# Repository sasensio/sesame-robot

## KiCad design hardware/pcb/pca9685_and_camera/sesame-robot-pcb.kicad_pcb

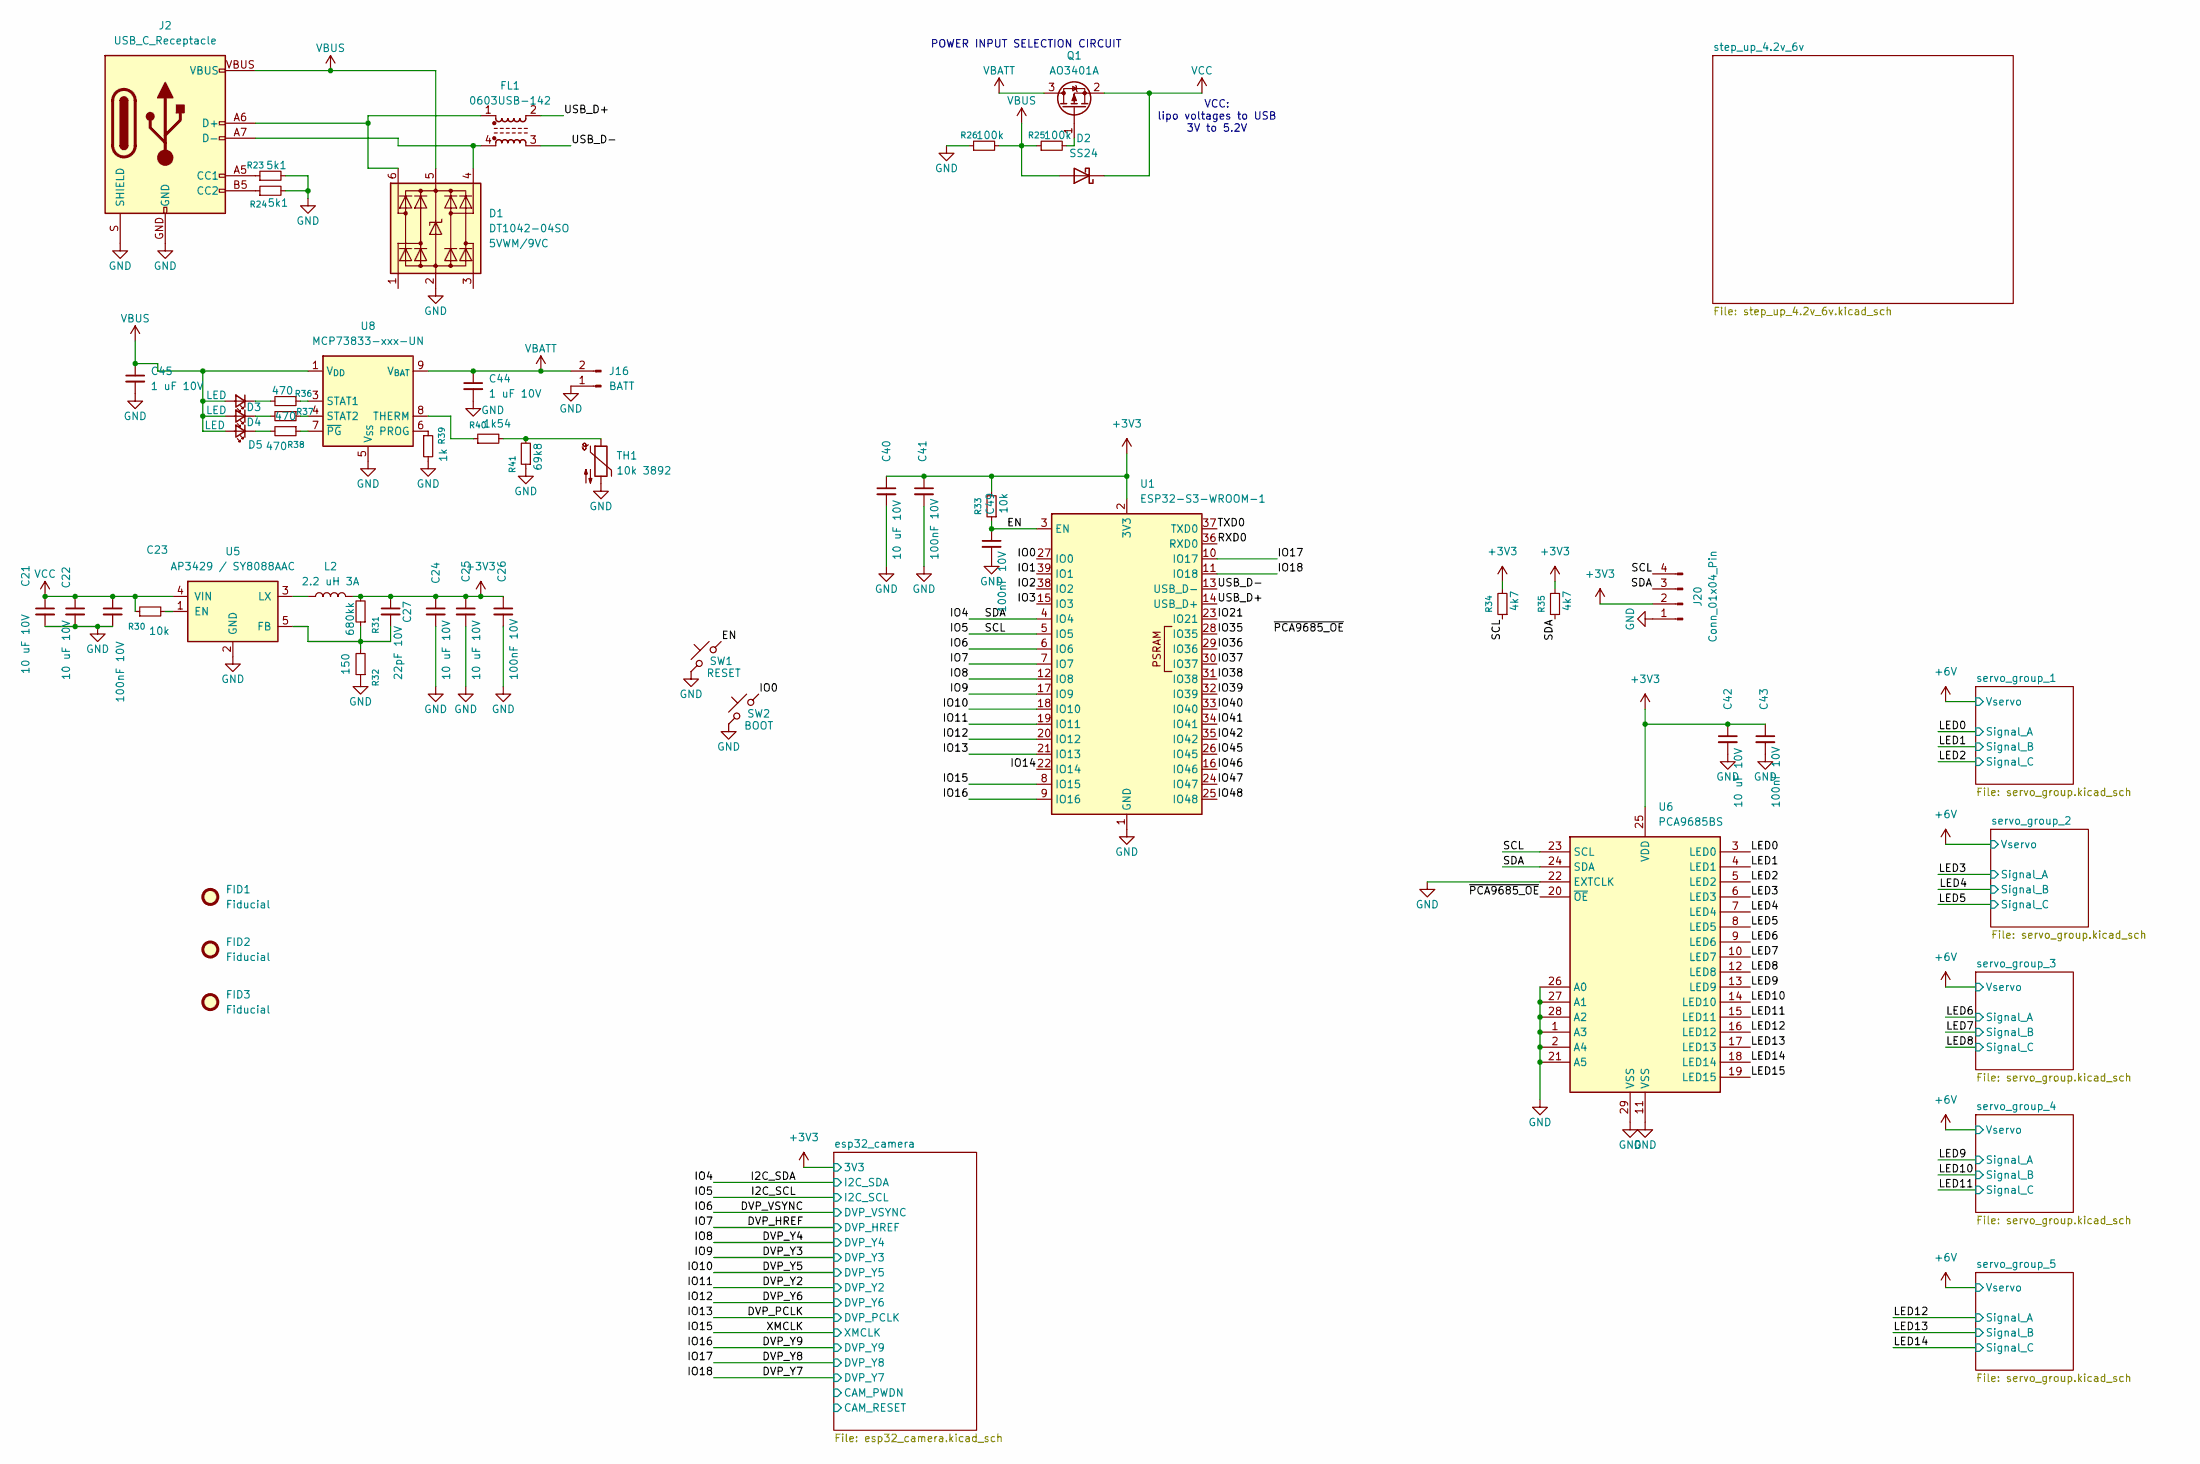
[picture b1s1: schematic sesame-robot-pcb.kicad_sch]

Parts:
C21, C22, C24, C25, C40, C42: 10 uF 10V; C_0603_1608Metric
C23, C26, C41, C43, C49: 100nF 10V; C_0402_1005Metric
C27: 22pF 10V; C_0402_1005Metric
C44, C45: 1 uF 10V; C_0603_1608Metric
D1: DT1042-04SO; SOT23-6; Rating 5VWM/9VC
D2: SS24; D_SMA
D3, D4, D5: LED; LED_0603_1608Metric
FID1, FID2, FID3: Fiducial; Fiducial_0.5mm_Mask1.5mm
FL1: 0603USB-142; L_CommonModeChoke_Coilcraft_0603USB
J2: USB_C_Receptacle; USB-C_16
J16: BATT; JST_PH_B2B-PH-K_1x02_P2.00mm_Vertical
J20: Conn_01x04_Pin; PinHeader_1x04_P2.54mm_Vertical
L2: 2.2 uH 3A; L_1206_3216Metric
Q1: AO3401A; SOT-23
R23, R24: 5k1; R_0402_1005Metric
R25, R26: 100k; R_0603_1608Metric
R30, R33: 10k; R_0603_1608Metric
R31: 680kk; R_0603_1608Metric
R32: 150; R_0603_1608Metric
R34, R35: 4k7; R_0603_1608Metric
R36, R37, R38: 470; R_0402_1005Metric
R39: 1k; R_0603_1608Metric
R40: 1k54; R_0402_1005Metric
R41: 69k8; R_0402_1005Metric
SW1: RESET; SW_SPST_EVQP2_MiddlePushTravel_H2.5mm
SW2: BOOT; SW_SPST_EVQP2_MiddlePushTravel_H2.5mm
TH1: 10k 3892; R_Axial_DIN0204_L3.6mm_D1.6mm_P2.54mm_Vertical
U1: ESP32-S3-WROOM-1; ESP32-S3-WROOM-1U
U5: AP3429 / SY8088AAC; SOT23-5
U6: PCA9685BS; QFN-28-1EP_6x6mm_P0.65mm_EP4.25x4.25mm
U8: MCP73833-xxx-UN; MSOP-10_3x3mm_P0.5mm

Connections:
+3V3: C24.1, C25.1, C26.1, C27.1, C40.1, C41.1, C42.1, C43.1, J20.2, L2.2, R31.2, R33.2, R34.2, R35.2, U1.2 (3V3), U6.25 (VDD); also elsewhere on the board
/DVP_HREF: U1.7 (IO7); also elsewhere on the board
/DVP_PCLK: U1.21 (IO13); also elsewhere on the board
/DVP_VSYNC: U1.6 (IO6); also elsewhere on the board
/DVP_Y2: U1.19 (IO11); also elsewhere on the board
/DVP_Y3: U1.17 (IO9); also elsewhere on the board
/DVP_Y4: U1.12 (IO8); also elsewhere on the board
/DVP_Y5: U1.18 (IO10); also elsewhere on the board
/DVP_Y6: U1.20 (IO12); also elsewhere on the board
/DVP_Y7: U1.11 (IO18); also elsewhere on the board
/DVP_Y8: U1.10 (IO17); also elsewhere on the board
/DVP_Y9: U1.9 (IO16); also elsewhere on the board
/EN: C49.1, R33.1, SW1.2, U1.3 (EN)
/I2C_SCL: J20.4, R34.1, U1.5 (IO5), U6.23 (SCL); also elsewhere on the board
/I2C_SDA: J20.3, R35.1, U1.4 (IO4), U6.24 (SDA); also elsewhere on the board
/IO0: SW2.2, U1.27 (IO0)
/IO1: U1.39 (IO1)
/IO2: U1.38 (IO2)
/IO3: U1.15 (IO3)
/IO14: U1.22 (IO14)
/IO15: U1.8 (IO15); also elsewhere on the board
/IO21: U1.23 (IO21)
/IO35: U1.28 (IO35)
/IO36: U1.29 (IO36)
/IO37: U1.30 (IO37)
/IO38: U1.31 (IO38)
/IO39: U1.32 (IO39)
/IO40: U1.33 (IO40)
/IO41: U1.34 (IO41)
/IO42: U1.35 (IO42)
/IO45: U1.26 (IO45)
/IO46: U1.16 (IO46)
/IO47: U1.24 (IO47)
/IO48: U1.25 (IO48)
/LED0: U6.3 (LED0); also elsewhere on the board
/LED1: U6.4 (LED1); also elsewhere on the board
/LED2: U6.5 (LED2); also elsewhere on the board
/LED3: U6.6 (LED3); also elsewhere on the board
/LED4: U6.7 (LED4); also elsewhere on the board
/LED5: U6.8 (LED5); also elsewhere on the board
/LED6: U6.9 (LED6); also elsewhere on the board
/LED7: U6.10 (LED7); also elsewhere on the board
/LED8: U6.12 (LED8); also elsewhere on the board
/LED9: U6.13 (LED9); also elsewhere on the board
/LED10: U6.14 (LED10); also elsewhere on the board
/LED11: U6.15 (LED11); also elsewhere on the board
/LED12: U6.16 (LED12); also elsewhere on the board
/LED13: U6.17 (LED13); also elsewhere on the board
/LED14: U6.18 (LED14); also elsewhere on the board
/LED15: U6.19 (LED15)
/RXD0: U1.36 (RXD0)
/TXD0: U1.37 (TXD0)
/USB_D+: FL1.2, U1.14 (USB_D+)
/USB_D-: FL1.3, U1.13 (USB_D-)
/~PCA9685_OE: U6.20 (~OE)
GND: C21.2, C22.2, C23.2, C24.2, C25.2, C26.2, C40.2, C41.2, C42.2, C43.2, C44.2, C45.2, C49.2, D1.2 (GND), J2.GND, J2.S (SHIELD), J16.1, J20.1, R23.2, R24.2, R26.1, R32.1, R39.2, R41.1, SW1.1, SW2.1, TH1.2, U1.1 (GND), U1.40 (GND), U1.41 (GND), U5.2 (GND), U6.1 (A3), U6.2 (A4), U6.11 (VSS), U6.21 (A5), U6.22 (EXTCLK), U6.26 (A0), U6.27 (A1), U6.28 (A2), U6.29 (VSS), U8.5 (V_{SS}); also elsewhere on the board
unnamed: D1.4 (I/O3), FL1.4, J2.A7 (D-), J2.B7 (D-)
unnamed: D1.6 (I/O4), FL1.1, J2.A6 (D+), J2.B6 (D+)
unnamed: D3.1 (K), R36.2
unnamed: D4.1 (K), R37.2
unnamed: D5.1 (K), R38.2
unnamed: J2.A5 (CC1), R23.1
unnamed: J2.B5 (CC2), R24.1
unnamed: Q1.1 (G), R25.2
unnamed: R40.2, R41.2, TH1.1
unnamed: R30.2, U5.1 (EN)
unnamed: C27.2, R31.1, R32.2, U5.5 (FB)
unnamed: L2.1, U5.3 (LX)
unnamed: R39.1, U8.6 (PROG)
unnamed: R36.1, U8.3 (STAT1)
unnamed: R37.1, U8.4 (STAT2)
unnamed: R40.1, U8.8 (THERM)
unnamed: R38.1, U8.7 (~PG)
VBATT: C44.1, J16.2, Q1.3 (D), U8.9 (V_{BAT}), U8.10 (V_{BAT})
VBUS: C45.1, D1.5 (VCC), D2.2 (A), D3.2 (A), D4.2 (A), D5.2 (A), J2.VBUS, R25.1, R26.2, U8.1 (V_{DD}), U8.2 (V_{DD})
VCC: C21.1, C22.1, C23.1, D2.1 (K), Q1.2 (S), R30.1, U5.4 (VIN); also elsewhere on the board

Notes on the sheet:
VCC: lipo voltages to USB 3V to 5.2V
POWER INPUT SELECTION CIRCUIT

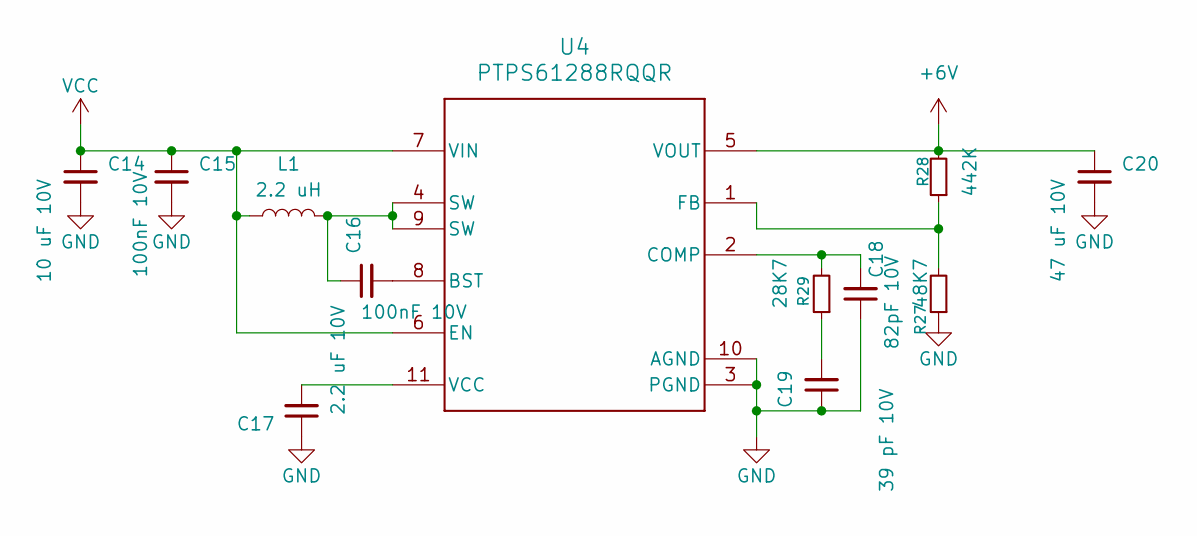
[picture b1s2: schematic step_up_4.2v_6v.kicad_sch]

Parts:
C14: 10 uF 10V; C_0603_1608Metric
C15, C16: 100nF 10V; C_0402_1005Metric
C17: 2.2 uF 10V; C_0603_1608Metric
C18: 82pF 10V; C_0402_1005Metric
C19: 39 pF 10V; C_0402_1005Metric
C20: 47 uF 10V; C_1206_3216Metric
L1: 2.2 uH; L_TDK_VLS6045EX_VLS6045AF; mpn# SRP5030HMT-1R0M
R27: 48K7; R_0603_1608Metric
R28: 442K; R_0603_1608Metric
R29: 28K7; R_0603_1608Metric
U4: PTPS61288RQQR; RQQ0011A-MFG

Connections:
+6V: C20.1, R28.2, U4.5 (VOUT); also elsewhere on the board
GND: C14.2, C15.2, C17.1, C18.1, C19.1, C20.2, R27.1, U4.3 (PGND), U4.10 (AGND); also elsewhere on the board
unnamed: C16.1, L1.2, U4.4 (SW), U4.9 (SW)
unnamed: C19.2, R29.1
unnamed: C16.2, U4.8 (BST)
unnamed: C18.2, R29.2, U4.2 (COMP)
unnamed: R27.2, R28.1, U4.1 (FB)
unnamed: C17.2, U4.11 (VCC)
VCC: C14.1, C15.1, L1.1, U4.6 (EN), U4.7 (VIN); also elsewhere on the board

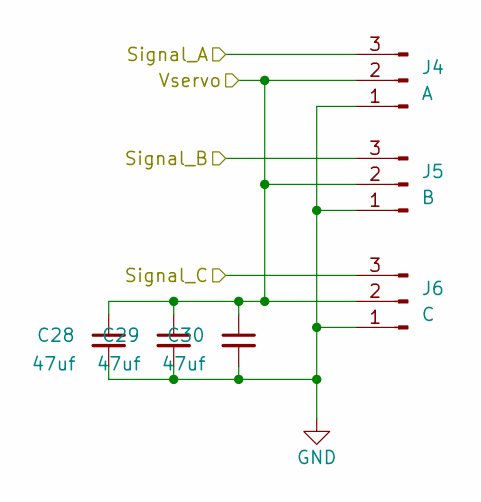
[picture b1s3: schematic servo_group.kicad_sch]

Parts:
C28, C29, C30: 47uf; C_1206_3216Metric
J4: A; PinHeader_1x03_P2.54mm_Vertical
J5: B; PinHeader_1x03_P2.54mm_Vertical
J6: C; PinHeader_1x03_P2.54mm_Vertical

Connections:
+6V: C28.1, C29.1, C30.1, J4.2, J5.2, J6.2; also elsewhere on the board
/LED0: J4.3; also elsewhere on the board
/LED1: J5.3; also elsewhere on the board
/LED2: J6.3; also elsewhere on the board
GND: C28.2, C29.2, C30.2, J4.1, J5.1, J6.1; also elsewhere on the board

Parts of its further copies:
C31, C32, C33, C34, C35, C36, C37, C38, C39, C46, C47, C48: 47uf; C_1206_3216Metric
J7, J10, J13, J17: A; PinHeader_1x03_P2.54mm_Vertical
J8, J11, J14, J18: B; PinHeader_1x03_P2.54mm_Vertical
J9, J12, J15, J19: C; PinHeader_1x03_P2.54mm_Vertical

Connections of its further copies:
+6V: C31.1, C32.1, C33.1, C34.1, C35.1, C36.1, C37.1, C38.1, C39.1, C46.1, C47.1, C48.1, J7.2, J8.2, J9.2, J10.2, J11.2, J12.2, J13.2, J14.2, J15.2, J17.2, J18.2, J19.2; also elsewhere on the board
/LED3: J7.3; also elsewhere on the board
/LED4: J8.3; also elsewhere on the board
/LED5: J9.3; also elsewhere on the board
/LED6: J10.3; also elsewhere on the board
/LED7: J11.3; also elsewhere on the board
/LED8: J12.3; also elsewhere on the board
/LED9: J13.3; also elsewhere on the board
/LED10: J14.3; also elsewhere on the board
/LED11: J15.3; also elsewhere on the board
/LED12: J17.3; also elsewhere on the board
/LED13: J18.3; also elsewhere on the board
/LED14: J19.3; also elsewhere on the board
GND: C31.2, C32.2, C33.2, C34.2, C35.2, C36.2, C37.2, C38.2, C39.2, C46.2, C47.2, C48.2, J7.1, J8.1, J9.1, J10.1, J11.1, J12.1, J13.1, J14.1, J15.1, J17.1, J18.1, J19.1; also elsewhere on the board

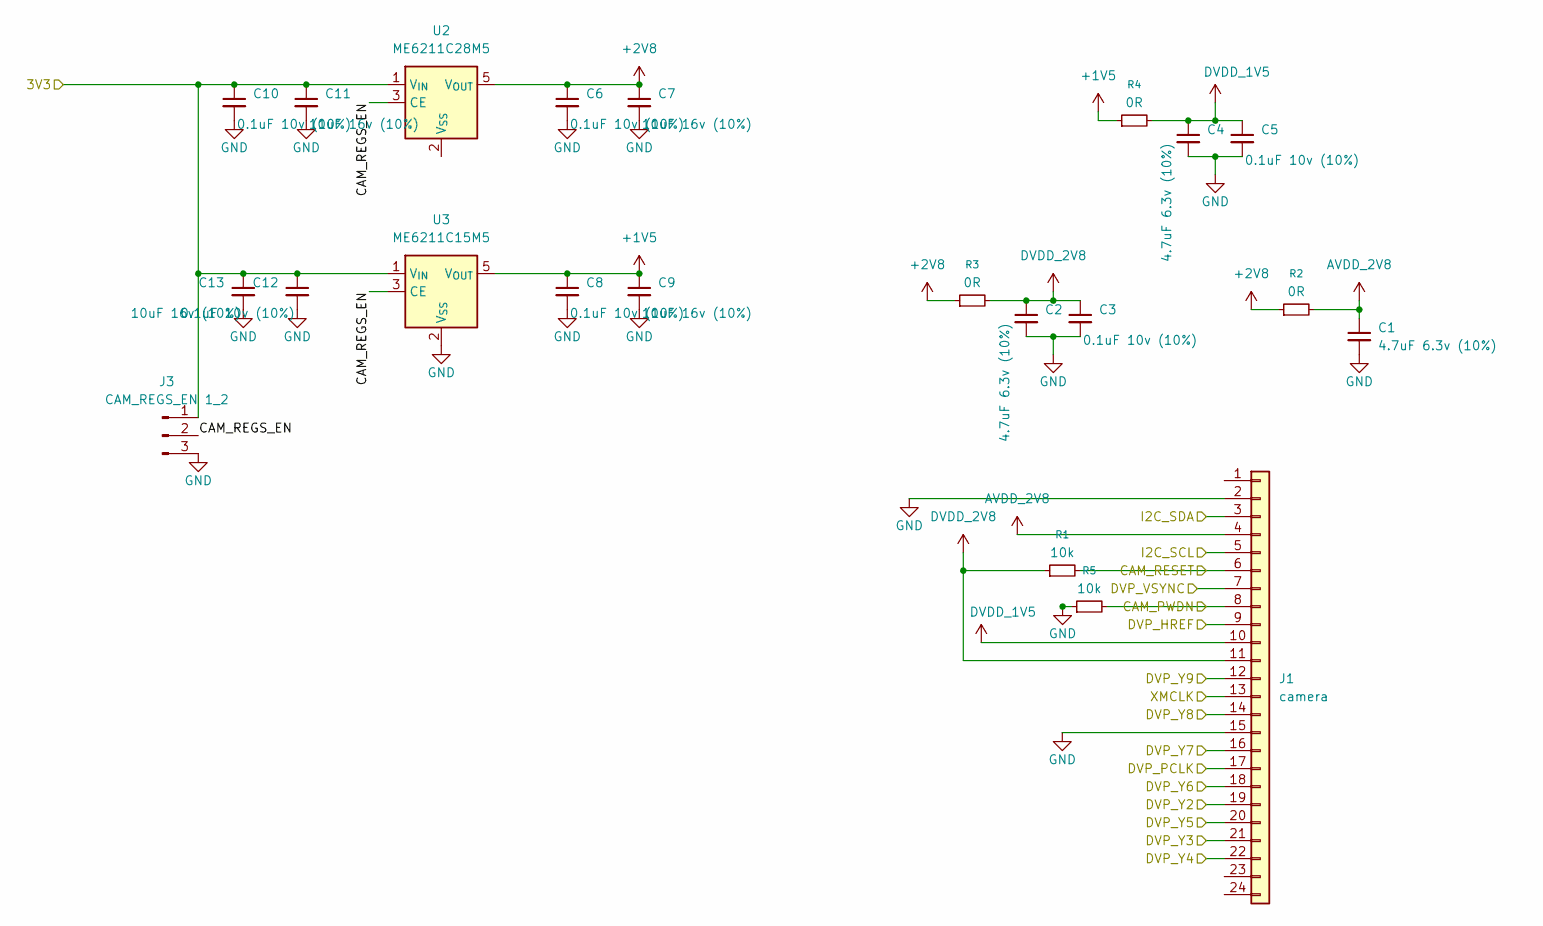
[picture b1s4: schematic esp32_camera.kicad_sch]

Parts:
C1, C2, C4: 4.7uF 6.3v (10%); C_0402_1005Metric
C3, C5, C6, C8, C10, C12: 0.1uF 10v (10%); C_0402_1005Metric
C7, C9, C11, C13: 10uF 16v (10%); C_0603_1608Metric
J1: camera; FPC_1x24_P0.5mm_Horizontal_DualContact
J3: CAM_REGS_EN 1_2; PinHeader_1x03_P2.00mm_Vertical
R1, R5: 10k; R_0603_1608Metric
R2, R3, R4: 0R; R_0402_1005Metric
U2: ME6211C28M5; SOT-23-5
U3: ME6211C15M5; SOT-23-5

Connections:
+1V5: C8.1, C9.1, R4.1, U3.5 (V_{OUT})
+2V8: C6.1, C7.1, R2.1, R3.1, U2.5 (V_{OUT})
+3V3: C10.1, C11.1, C12.1, C13.1, J3.1, U2.1 (V_{IN}), U3.1 (V_{IN}); also elsewhere on the board
/DVP_HREF: J1.9; also elsewhere on the board
/DVP_PCLK: J1.17; also elsewhere on the board
/DVP_VSYNC: J1.7; also elsewhere on the board
/DVP_Y2: J1.19; also elsewhere on the board
/DVP_Y3: J1.21; also elsewhere on the board
/DVP_Y4: J1.22; also elsewhere on the board
/DVP_Y5: J1.20; also elsewhere on the board
/DVP_Y6: J1.18; also elsewhere on the board
/DVP_Y7: J1.16; also elsewhere on the board
/DVP_Y8: J1.14; also elsewhere on the board
/DVP_Y9: J1.12; also elsewhere on the board
/I2C_SCL: J1.5; also elsewhere on the board
/I2C_SDA: J1.3; also elsewhere on the board
/IO15: J1.13; also elsewhere on the board
/esp32_camera/CAM_PWDN: J1.8, R5.2
/esp32_camera/CAM_REGS_EN: J3.2, U2.3 (CE), U3.3 (CE)
/esp32_camera/CAM_RESET: J1.6, R1.2
AVDD_2V8: C1.1, J1.4, R2.2
DVDD_1V5: C4.1, C5.1, J1.10, R4.2
DVDD_2V8: C2.1, C3.1, J1.11, R1.1, R3.2
GND: C1.2, C2.2, C3.2, C4.2, C5.2, C6.2, C7.2, C8.2, C9.2, C10.2, C11.2, C12.2, C13.2, J1.2, J1.15, J3.3, R5.1, U3.2 (V_{SS}); also elsewhere on the board

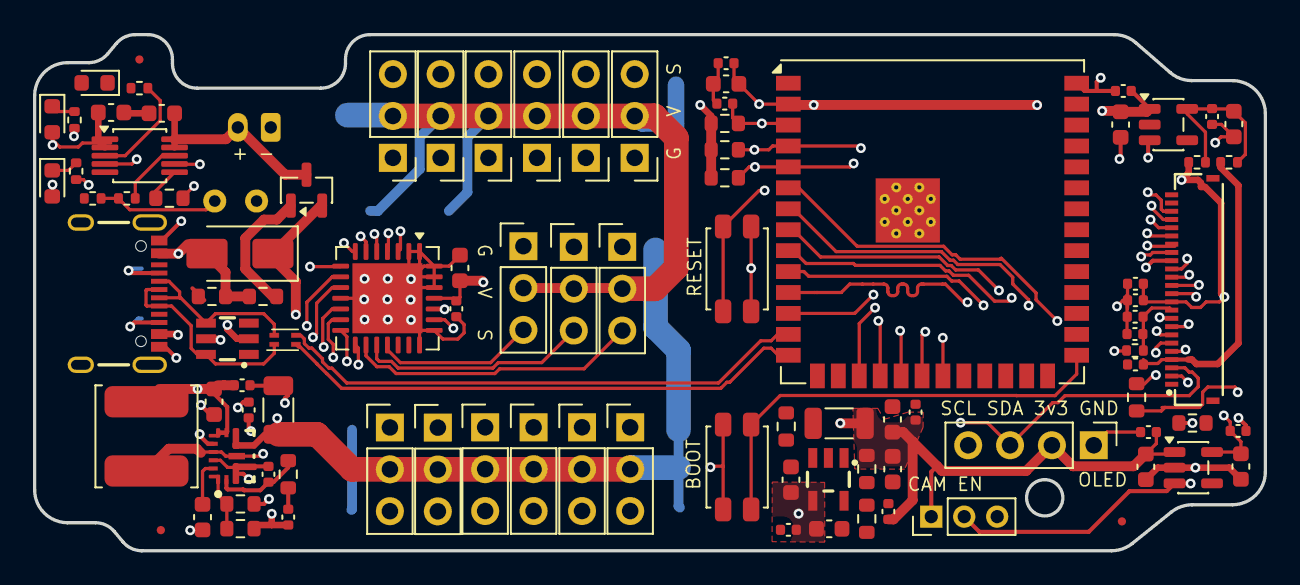
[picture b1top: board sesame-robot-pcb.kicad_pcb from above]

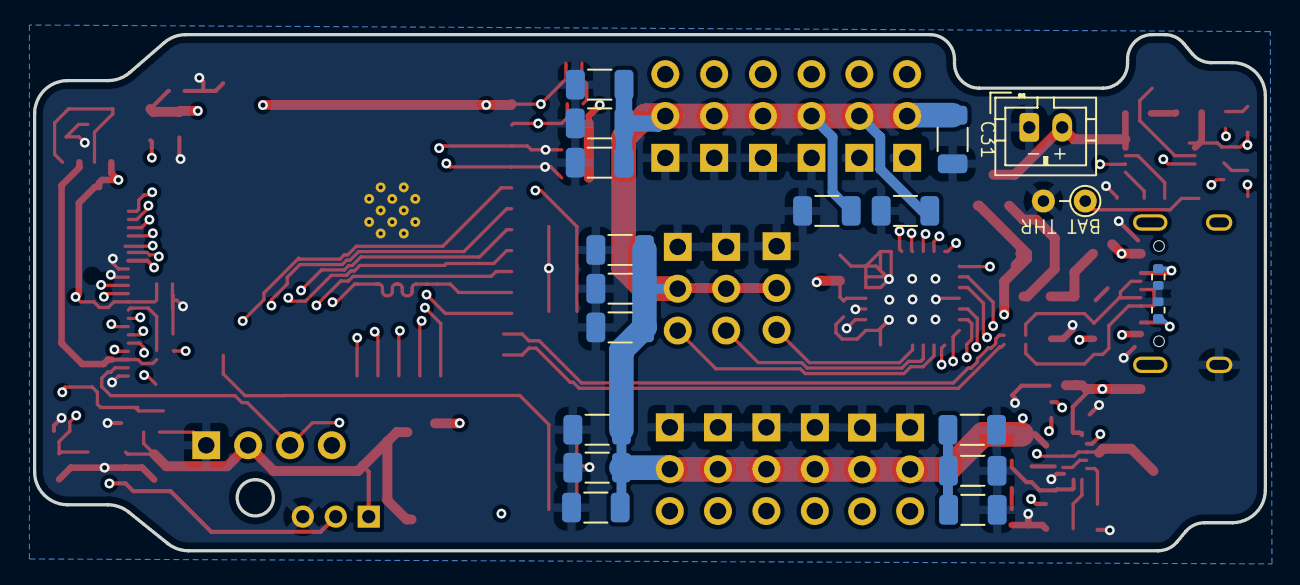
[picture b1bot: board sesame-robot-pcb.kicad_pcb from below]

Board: 4 copper layers, 74.7 x 31.3 mm, 115 parts (19 on the bottom side), 70 nets.

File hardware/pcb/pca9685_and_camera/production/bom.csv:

Designator,Footprint,Quantity,Value,LCSC Part #
"C1, C2, C4",0402,3,4.7uF 6.3v (10%),
"C10, C12, C3, C5, C6, C8",0402,6,0.1uF 10v (10%),
"C11, C13, C7, C9",0603,4,10uF 16v (10%),
"C14, C21, C22, C24, C25, C40, C42",0603,7,10 uF 10V,
"C15, C16, C23, C26, C41, C43, C49",0402,7,100nF 10V,
C17,0603,1,2.2 uF 10V,
C18,0402,1,82pF 10V,
C19,0402,1,39 pF 10V,
C20,1206,1,47 uF 10V,
C27,0603,1,22pF 10V,
"C28, C29, C30, C31, C32, C33, C34, C35, C36, C37, C38, C39, C46, C47, C48",1206,15,47uf,
"C44, C45",0603,2,1 uF 10V,
D1,SOT23-6,1,DT1042-04SO,
D2,D_SMA,1,SS24,
"D3, D4, D5",0603,3,LED,
FL1,L_CommonModeChoke_Coilcraft_0603USB,1,0603USB-142,
J1,FPC_1x24_P0.5mm_Horizontal_DualContact,1,camera,
"J10, J13, J17, J4, J7",PinHeader_1x03_P2.54mm_Vertical,5,A,
"J11, J14, J18, J5, J8",PinHeader_1x03_P2.54mm_Vertical,5,B,
"J12, J15, J19, J6, J9",PinHeader_1x03_P2.54mm_Vertical,5,C,
J16,JST_PH_B2B-PH-K_1x02_P2.00mm_Vertical,1,BATT,
J2,USB-C_16,1,USB_C_Receptacle,
J20,PinHeader_1x04_P2.54mm_Vertical,1,Conn_01x04_Pin,
J3,PinHeader_1x03_P2.00mm_Vertical,1,CAM_REGS_EN 1_2,
L1,L_TDK_VLS6045EX_VLS6045AF,1,2.2 uH,
L2,1206,1,2.2 uH 3A,
Q1,SOT-23,1,AO3401A,
"R1, R30, R33, R5",0603,4,10k,
"R2, R3, R4",0402,3,0R,
"R23, R24",0402,2,5k1,
"R25, R26",0603,2,100k,
R27,0603,1,48K7,
R28,0603,1,442K,
R29,0603,1,28K7,
R31,0603,1,680kk,
R32,0603,1,150,
"R34, R35",0603,2,4k7,
"R36, R37, R38",0402,3,470,
R39,0603,1,1k,
R40,0402,1,1k54,
R41,0402,1,69k8,
SW1,SW_SPST_EVQP2_MiddlePushTravel_H2.5mm,1,RESET,
SW2,SW_SPST_EVQP2_MiddlePushTravel_H2.5mm,1,BOOT,
TH1,R_Axial_DIN0204_L3.6mm_D1.6mm_P2.54mm_Vertical,1,10k 3892,
U1,ESP32-S3-WROOM-1U,1,ESP32-S3-WROOM-1,
U2,SOT-23-5,1,ME6211C28M5,
U3,SOT-23-5,1,ME6211C15M5,
U4,RQQ0011A-MFG,1,PTPS61288RQQR,
U5,SOT23-5,1,AP3429 / SY8088AAC,
U6,QFN-28-1EP_6x6mm_P0.65mm_EP4.25x4.25mm,1,PCA9685BS,
U8,MSOP-10_3x3mm_P0.5mm,1,MCP73833-xxx-UN,

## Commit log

2026-03-25 Add tutorial button to README
    Added a tutorial button and updated the greeting.
2026-03-29 Fix duplicate Tutorial button
2026-04-13 Initial plan
2026-04-13 Add HAL files for ESP32-CAM and ESP32-S3-CAM with PCA9685 servo driver support
    Agent-Logs-Url: https://github.com/sasensio/sesame-robot/sessions/312de17f-44b5-4109-b239-108d2f71cb64
2026-04-16 Fix ESP32-CAM I2C pins to use accessible header pins GPIO 14/15 instead of internal camera SCCB GPIO 26/27
    Agent-Logs-Url: https://github.com/sasensio/sesame-robot/sessions/0998b293-fa4c-4913-8a36-1bcec4ed07fb
2026-04-19 added esp23-cam carrier
2026-04-20 feat: improve camera reliability, reduce servo idle power, and add LED control
    - add optional PCA9685 servo auto-release to reduce idle power draw on camera boards
    - keep camera in high-FPS mode for 30 seconds after movement stops
    - harden camera OFF->ON lifecycle with deinit, delayed power-up, reinit retries, and frame-failure recovery
    - add camera LED support in HAL, firmware settings API, and web UI toggle near camera control
    - improve web stream reconnect behavior with cache-busted URLs and retry cleanup
    - update firmware and HAL documentation for new camera/servo behavior and settings endpoints
2026-04-22 feat: implement micro-ROS firmware + ArUco positioning ROS 2 package
    Agent-Logs-Url: https://github.com/sasensio/sesame-robot/sessions/51159b44-d19c-4aed-acf7-b9300434286d
2026-04-22 fix: use LaunchConfiguration for agent_port in log message
    Agent-Logs-Url: https://github.com/sasensio/sesame-robot/sessions/51159b44-d19c-4aed-acf7-b9300434286d
